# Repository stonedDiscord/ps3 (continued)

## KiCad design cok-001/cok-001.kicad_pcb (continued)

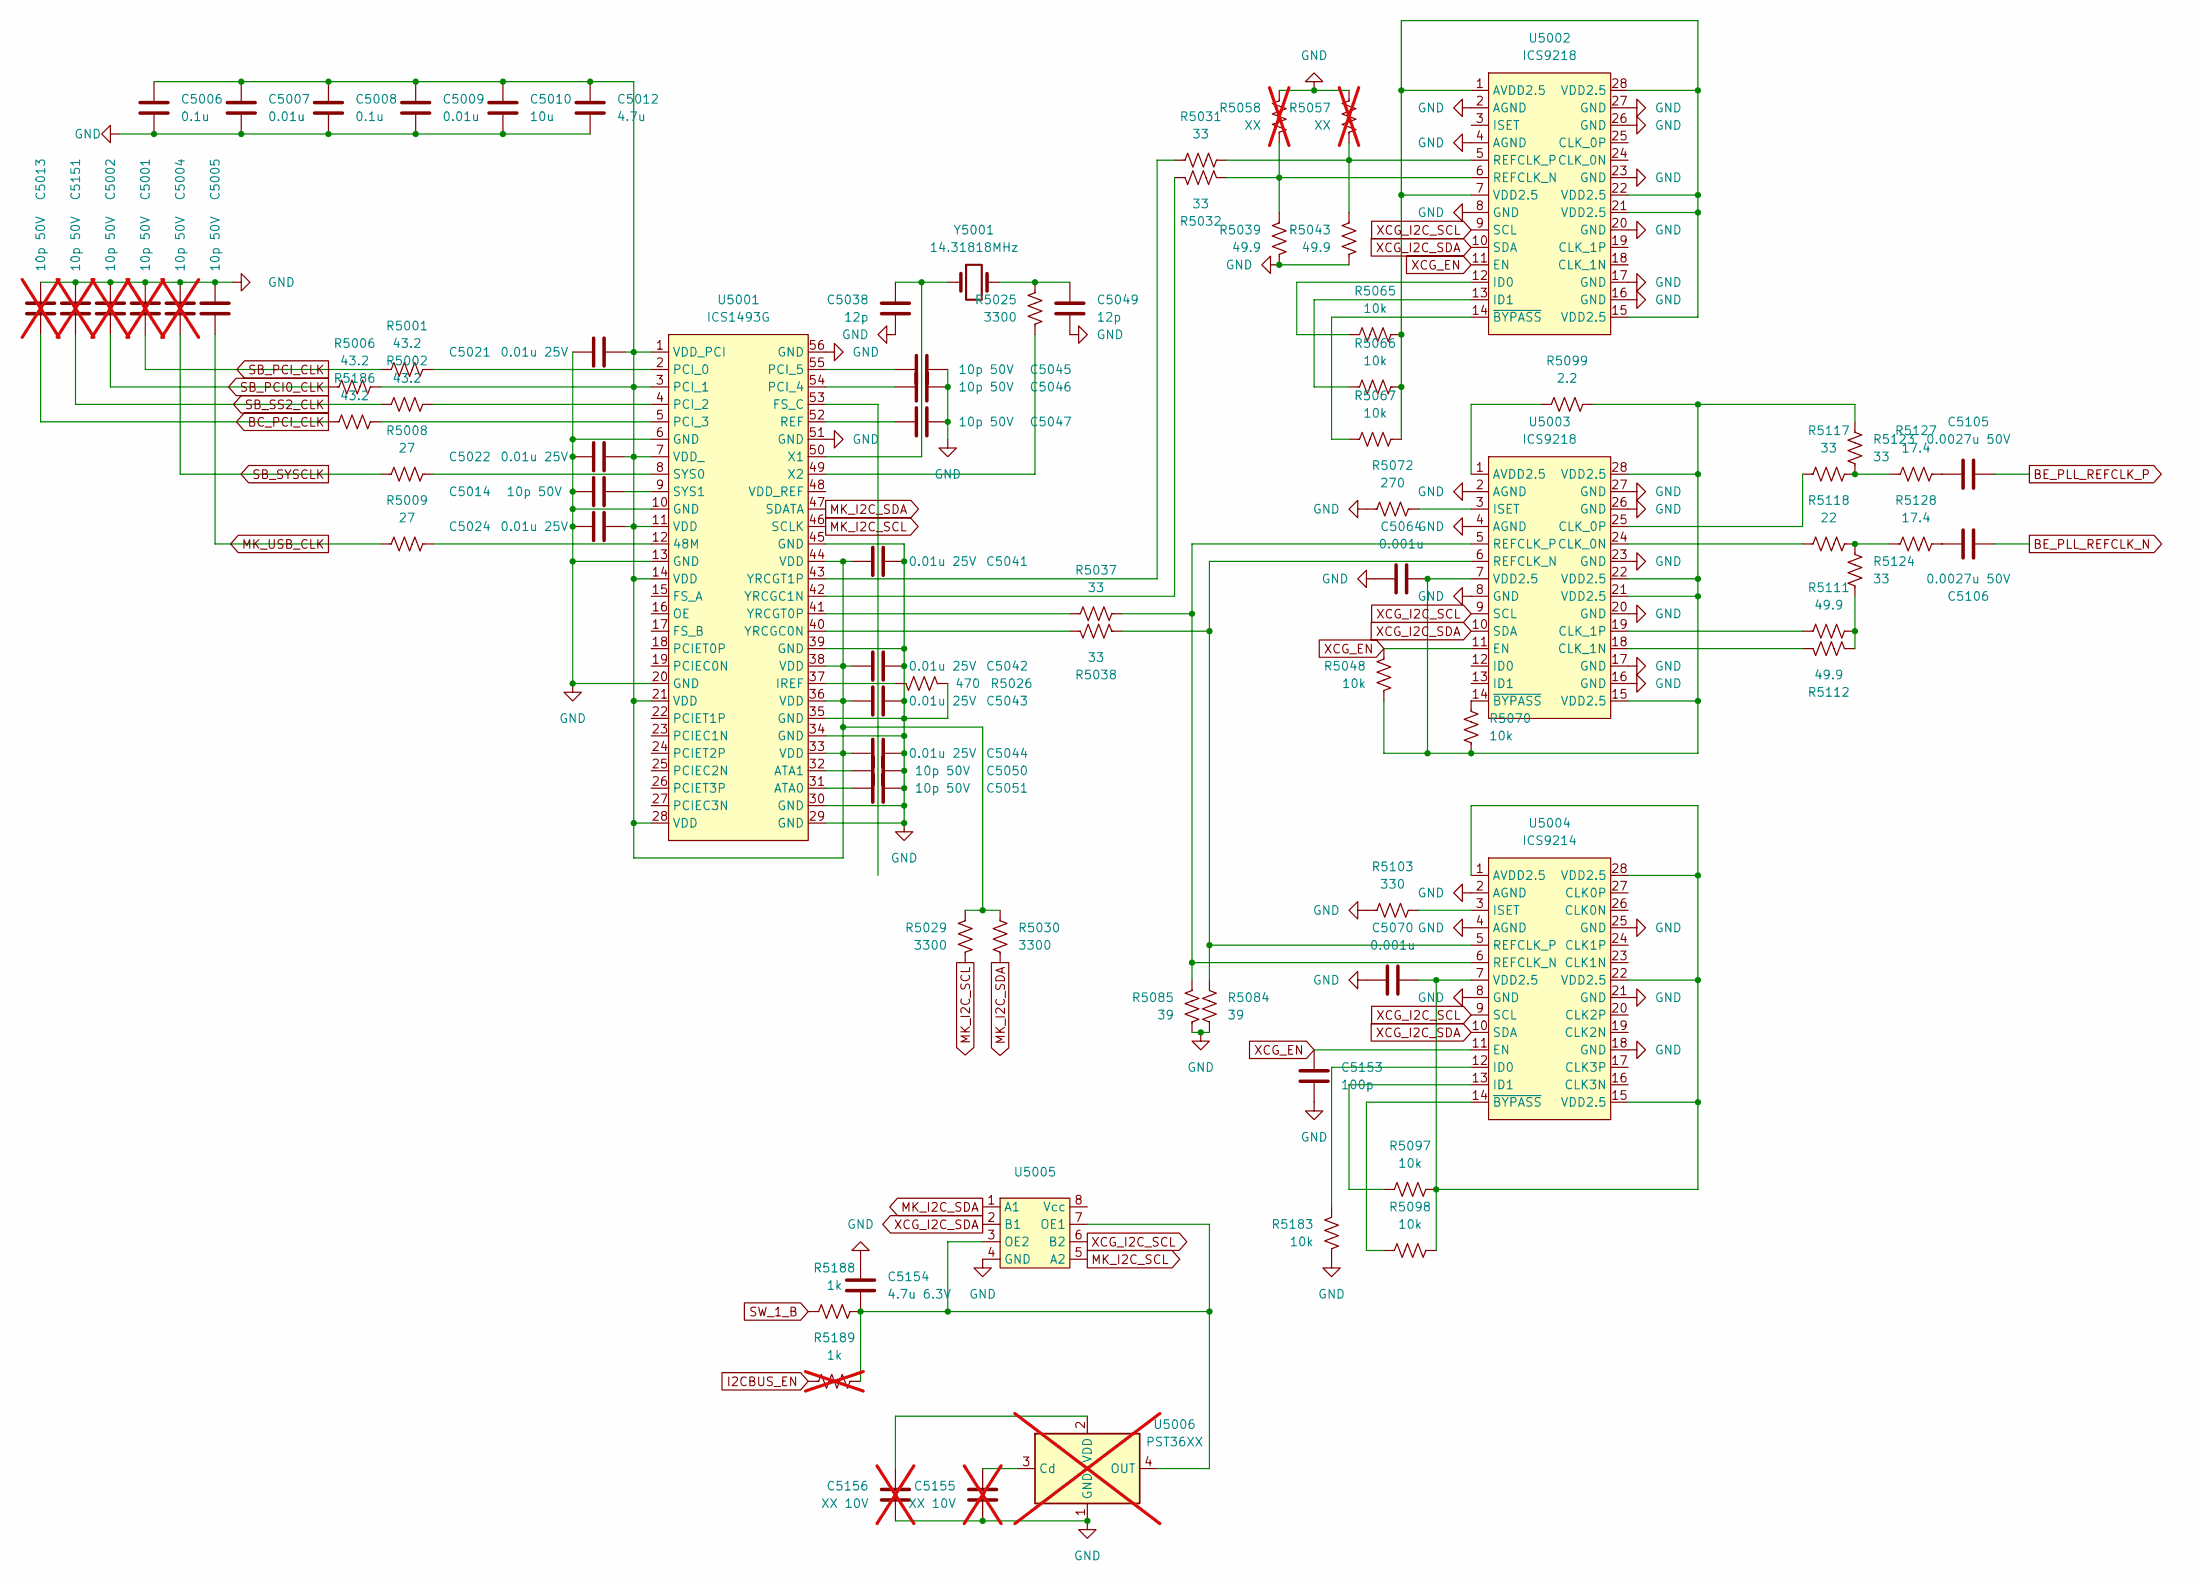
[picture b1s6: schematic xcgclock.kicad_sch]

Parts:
C5001, C5002, C5004, C5013, C5151: 10p 50V; C_0402_1005Metric; not fitted
C5005, C5014, C5045, C5046, C5047, C5050, C5051: 10p 50V; C_0402_1005Metric
C5006, C5008: 0.1u; C_0402_1005Metric
C5007, C5009: 0.01u; C_0402_1005Metric
C5010: 10u; C_0402_1005Metric
C5012: 4.7u; C_0805_2012Metric
C5021, C5022, C5024, C5041, C5042, C5043, C5044: 0.01u 25V; C_0402_1005Metric
C5038, C5049: 12p; C_0402_1005Metric
C5064, C5070: 0.001u; C_0402_1005Metric
C5105, C5106: 0.0027u 50V; C_0402_1005Metric
C5153: 100p; C_0402_1005Metric
C5154: 4.7u 6.3V; C_0603_1608Metric
C5155, C5156: XX 10V; C_0402_1005Metric; not fitted
R5001, R5002, R5006, R5186: 43.2; R_0402_1005Metric
R5008, R5009: 27; R_0402_1005Metric
R5025, R5029, R5030: 3300; R_0402_1005Metric
R5026: 470; R_0402_1005Metric
R5031, R5032, R5037, R5038, R5117, R5123, R5124: 33; R_0402_1005Metric
R5039, R5043, R5111, R5112: 49.9; R_0402_1005Metric
R5048, R5065, R5066, R5067, R5070, R5097, R5098, R5183: 10k; R_0402_1005Metric
R5057, R5058: XX; R_0402_1005Metric; not fitted
R5072: 270; R_0402_1005Metric
R5084, R5085: 39; R_0402_1005Metric
R5099: 2.2; R_0603_1608Metric
R5103: 330; R_0402_1005Metric
R5118: 22; R_0402_1005Metric
R5127, R5128: 17.4; R_0402_1005Metric
R5188: 1k; R_0402_1005Metric
R5189: 1k; R_0402_1005Metric; not fitted
U5001: ICS1493G; TSSOP-56_6.1x14mm_P0.5mm
U5002, U5003: ICS9218; QSOP-28_3.9x9.9mm_P0.635mm
U5004: ICS9214; QSOP-28_3.9x9.9mm_P0.635mm
U5005: VSSOP-8_2.3x2mm_P0.5mm
U5006: PST36XX; SC-82AB; not fitted
Y5001: 14.31818MHz; Crystal_SMD_Abracon_ABM3-2Pin_5.0x3.2mm

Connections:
BC_PCI_CLK: C5013.2, R5186.1
BE_PLL_REFCLK_N: C5106.2
BE_PLL_REFCLK_P: C5105.2
GND: C5001.1, C5002.1, C5004.1, C5005.1, C5006.2, C5007.2, C5008.2, C5009.2, C5010.2, C5012.2, C5013.1, C5014.1, C5021.1, C5022.1, C5024.1, C5038.2, C5041.1, C5042.1, C5043.1, C5044.1, C5045.1, C5046.1, C5047.1, C5049.2, C5050.1, C5051.1, C5064.1, C5070.1, C5151.1, C5153.2, C5154.1, C5155.2, C5156.2, R5026.2, R5039.2, R5043.2, R5057.1, R5058.1, R5072.1, R5084.2, R5085.2, R5103.1, R5183.1, U5001.6 (GND), U5001.10 (GND), U5001.13 (GND), U5001.20 (GND), U5001.29 (GND), U5001.30 (GND), U5001.34 (GND), U5001.35 (GND), U5001.39 (GND), U5001.45 (GND), U5001.51 (GND), U5001.56 (GND), U5002.2 (AGND), U5002.4 (AGND), U5002.8 (GND), U5002.16 (GND), U5002.17 (GND), U5002.20 (GND), U5002.23 (GND), U5002.26 (GND), U5002.27 (GND), U5003.2 (AGND), U5003.4 (AGND), U5003.8 (GND), U5003.16 (GND), U5003.17 (GND), U5003.20 (GND), U5003.23 (GND), U5003.26 (GND), U5003.27 (GND), U5004.2 (AGND), U5004.4 (AGND), U5004.8 (GND), U5004.18 (GND), U5004.21 (GND), U5004.25 (GND), U5005.4 (GND), U5006.1 (GND); also elsewhere on the board
I2CBUS_EN: R5189.1
MK_I2C_SCL: R5029.2, U5001.46 (SCLK), U5005.5 (A2); also elsewhere on the board
MK_I2C_SDA: R5030.2, U5001.47 (SDATA), U5005.1 (A1); also elsewhere on the board
MK_USB_CLK: C5005.2, R5009.1; also elsewhere on the board
unnamed: C5049.1, R5025.1, Y5001.2
unnamed: C5064.2, R5048.1, R5070.1, R5099.2, R5123.2, U5003.7 (VDD2.5), U5003.15 (VDD2.5), U5003.21 (VDD2.5), U5003.22 (VDD2.5), U5003.28 (VDD2.5)
unnamed: C5105.1, R5127.2
unnamed: C5106.1, R5128.2
unnamed: R5111.2, R5112.2, R5124.1
unnamed: R5117.2, R5123.1, R5127.1
unnamed: R5118.2, R5124.2, R5128.1
unnamed: R5009.2, U5001.12 (48M)
unnamed: C5051.2, U5001.31 (ATA0)
unnamed: C5050.2, U5001.32 (ATA1)
unnamed: R5026.1, U5001.37 (IREF)
unnamed: R5001.2, U5001.2 (PCI_0)
unnamed: C5006.1, C5007.1, C5008.1, C5009.1, C5010.1, C5012.1, C5021.2, C5022.2, C5024.2, C5041.2, C5042.2, C5043.2, C5044.2, R5006.2, R5029.1, R5030.1, U5001.1 (VDD_PCI), U5001.3 (PCI_1), U5001.7 (VDD_), U5001.11 (VDD), U5001.14 (VDD), U5001.21 (VDD), U5001.28 (VDD), U5001.33 (VDD), U5001.36 (VDD), U5001.38 (VDD), U5001.44 (VDD)
unnamed: R5002.2, U5001.4 (PCI_2)
unnamed: R5186.2, U5001.5 (PCI_3)
unnamed: C5046.2, U5001.54 (PCI_4)
unnamed: C5045.2, U5001.55 (PCI_5)
unnamed: C5047.2, U5001.52 (REF)
unnamed: R5008.2, U5001.8 (SYS0)
unnamed: C5014.2, U5001.9 (SYS1)
unnamed: C5038.1, U5001.50 (X1), Y5001.1
unnamed: R5025.2, U5001.49 (X2)
unnamed: R5038.1, U5001.40 (YRCGC0N)
unnamed: R5032.1, U5001.42 (YRCGC1N)
unnamed: R5037.1, U5001.41 (YRCGT0P)
unnamed: R5031.1, U5001.43 (YRCGT1P)
unnamed: R5065.1, R5066.1, R5067.1, U5002.1 (AVDD2.5), U5002.7 (VDD2.5), U5002.15 (VDD2.5), U5002.21 (VDD2.5), U5002.22 (VDD2.5), U5002.28 (VDD2.5)
unnamed: R5065.2, U5002.12 (ID0)
unnamed: R5066.2, U5002.13 (ID1)
unnamed: R5032.2, R5039.1, R5058.2, U5002.6 (REFCLK_N)
unnamed: R5031.2, R5043.1, R5057.2, U5002.5 (REFCLK_P)
unnamed: R5067.2, U5002.14 (~BYPASS)
unnamed: R5099.1, U5003.1 (AVDD2.5)
unnamed: R5118.1, U5003.24 (CLK_0N)
unnamed: R5117.1, U5003.25 (CLK_0P)
unnamed: R5112.1, U5003.18 (CLK_1N)
unnamed: R5111.1, U5003.19 (CLK_1P)
unnamed: R5072.2, U5003.3 (ISET)
unnamed: R5038.2, R5084.1, U5003.6 (REFCLK_N), U5004.5 (REFCLK_P)
unnamed: R5037.2, R5085.1, U5003.5 (REFCLK_P), U5004.6 (REFCLK_N)
unnamed: R5070.2, U5003.14 (~BYPASS)
unnamed: C5070.2, R5097.2, R5098.2, U5004.1 (AVDD2.5), U5004.7 (VDD2.5), U5004.15 (VDD2.5), U5004.22 (VDD2.5), U5004.28 (VDD2.5)
unnamed: R5183.2, U5004.12 (ID0)
unnamed: R5097.1, U5004.13 (ID1)
unnamed: R5103.2, U5004.3 (ISET)
unnamed: R5098.1, U5004.14 (~BYPASS)
unnamed: C5154.2, R5188.2, R5189.2, U5005.3 (OE2), U5005.7 (OE1), U5006.4 (OUT)
unnamed: C5155.1, U5006.3 (Cd)
unnamed: C5156.1, U5006.2 (VDD)
SB_PCI0_CLK: C5002.2, R5006.1; also elsewhere on the board
SB_PCI_CLK: C5001.2, R5001.1; also elsewhere on the board
SB_SS2_CLK: C5151.2, R5002.1
SB_SYSCLK: C5004.2, R5008.1; also elsewhere on the board
SW_1_B: R5188.1; also elsewhere on the board
XCG_EN: C5153.1, R5048.2, U5002.11 (EN), U5003.11 (EN), U5004.11 (EN); also elsewhere on the board
XCG_I2C_SCL: U5002.9 (SCL), U5003.9 (SCL), U5004.9 (SCL), U5005.6 (B2)
XCG_I2C_SDA: U5002.10 (SDA), U5003.10 (SDA), U5004.10 (SDA), U5005.2 (B1)
